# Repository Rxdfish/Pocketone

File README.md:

# Pocketone
A compact midi board that fits into any pocket and still has a lot of features 

Inspiration came from this Repo with brilliant tutorial: [have a look]([https://github.com/SharKingStudios/Starbie/tree/main](https://github.com/KaiPereira/MIDI-Keypad/blob/master/README.md))

# What is this

Pocketone is a project, made for the [Half life](https://halflife.hackclub.com) by Hackclub programm. It is an MIDI keyboard with compact design and lots of features. It can be used to create music inputs for a computer or laptop.

The Board features a Microcontroller, display, buttons, and capacitive sensors in a compact PCB design. It is USB powered and easy to build.

# Project status

The project is half finished but more features and maybe tutorial will come soon.

# Motivation

The main motivation is of course the Half Life (LINK) program by hackclub. It was designed in week three of the project where the task was to create a music PCB. Other than that, I really wanted to design a PCB for a long time now and it definitely won’t be my last one. It was quite som challenge to cook that midi board up and its not nearly finished but im proud of my result.

# Project journaling

Via the [Half life](https://halflife.hackclub.com) by Hackclub programm, several Journal entries have been made either in timelaps form or as written entry to track the project. 

# Assembly

The assembly should be quite beginnerfriendly. The board itself has not many part and is partly prefabricated. All remaining components are easy to be soldered by hand.

# Schematic and components

The board is powered by the Waveshare ESP32-S3-ZERO. It provides the power and data connector with an onboard USB-receptacle. The board also features a keyboard in form of capacitive sensors and a small OLED display. Furthermore it has 3 fader sliders and 8 preassure sensor pads. Everything is made possible by an GPIO expander and a MUX.

# PCB

The PCB is a simple 2 layer PCB. NOthing special about it 

# Firmware

Sadly there is no firmware yet.

# BOM

This is the funding BOM but there is another BOM for all parts and the PCB manufacturing, which is out of budget unfortuenately.

PCB manuf. 
price: 19.30$

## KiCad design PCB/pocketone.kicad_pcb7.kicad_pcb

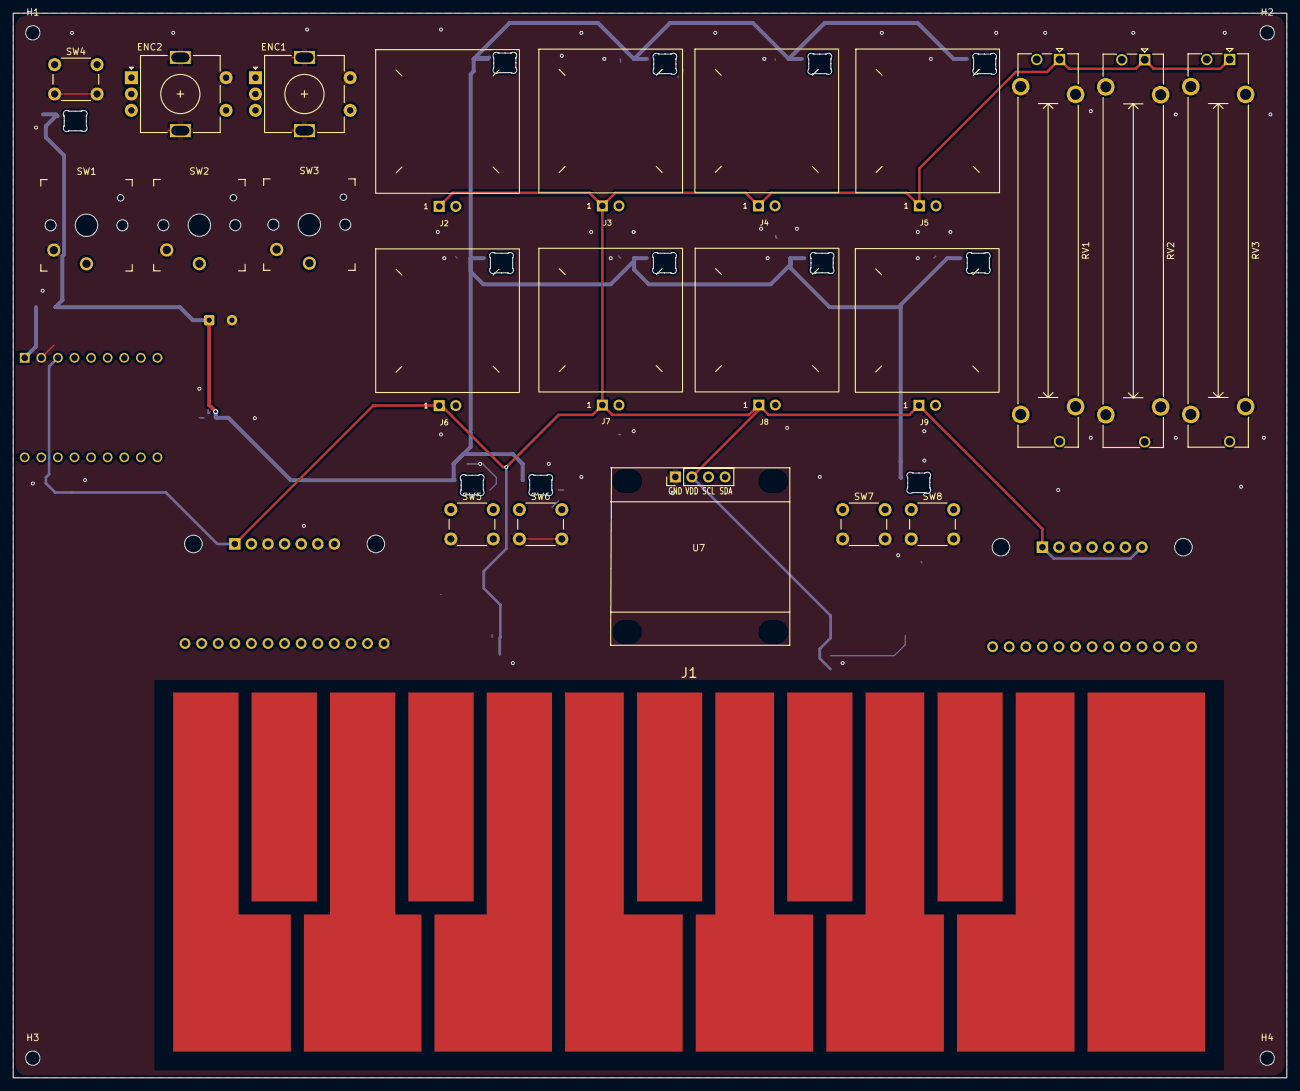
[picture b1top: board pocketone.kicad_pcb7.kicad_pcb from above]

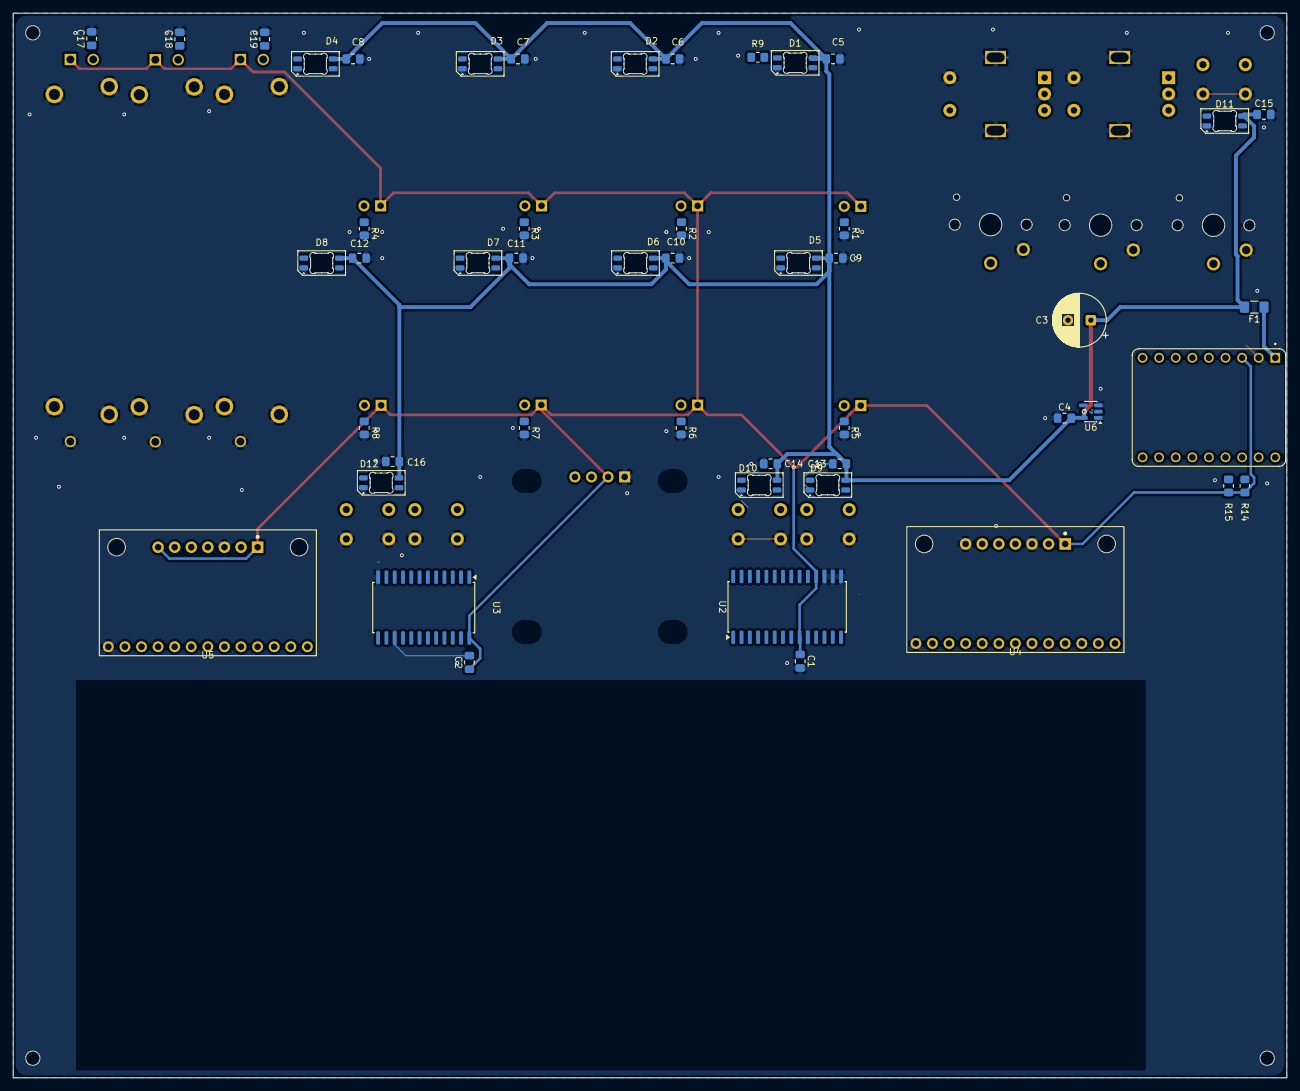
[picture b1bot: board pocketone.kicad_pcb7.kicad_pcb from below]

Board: 2 copper layers, 195.0 x 163.0 mm, 76 parts (49 on the bottom side), 63 nets.

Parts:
C1, C2, C4, C17, C18, C19: 100nF; C_0805_2012Metric_Pad1.18x1.45mm_HandSolder
C3: 470uF; CP_Radial_D8.0mm_P3.50mm
C5, C6, C7, C8, C9, C10, C11, C12, C13, C14, C15, C16: 100n; C_0805_2012Metric_Pad1.18x1.45mm_HandSolder
D1, D2, D3, D4, D5, D6, D7, D8, D9, D10, D11, D12: SK6812MINI-E; LED_SK6812MINI-E_3.2x2.8mm_P1.5mm_ReverseMount
ENC1, ENC2: RotaryEncoder_Switch_MP; RotaryEncoder_Alps_EC11E-Switch_Vertical_H20mm
F1: Polyfuse; Fuse_1206_3216Metric_Pad1.42x1.75mm_HandSolder
H1, H2, H3, H4: MountingHole_2.2mm_M2
J1: CAPACITIVE TOUCH BUTTONS; TouchKeys_1Octave
J2, J3, J4, J5, J6, J7, J8, J9: Conn_01x02; FSR402_Pad_22mm
R1, R2, R3, R4, R5, R6, R7, R8: 10k; R_0805_2012Metric_Pad1.20x1.40mm_HandSolder
R9: 330 O; R_0805_2012Metric_Pad1.20x1.40mm_HandSolder
R14, R15: 4.7kO; R_0805_2012Metric_Pad1.20x1.40mm_HandSolder
RV1, RV2, RV3: Slider; Potentiometer_Bourns_PTA4543_Single_Slide
SW1, SW2, SW3: SW_Push; Kailh Choc Low-Profile Switches
SW4, SW5, SW6, SW7, SW8: SW_Push; SW_PUSH_6mm
U1: Waveshare ESP32-S3-ZERO; Waveshare ESP32-S3-Zero
U2: MCP23017x-x-SO; SOIC-28W_7.5x17.9mm_P1.27mm
U3: CD74HC4067M; SOIC-24W_7.5x15.4mm_P1.27mm
U4, U5: MPR121 BREAKOUT; Adafruit_MPR121_STEMMA_QT
U6: 74AHCT1G125; SOT-23-5
U7: Conn_01x04; Display_128x64_096_I2C

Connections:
+3V3: C1.1, C2.1, J2.1, J3.1, J4.1, J5.1, J6.1, J7.1, J8.1, J9.1, R14.1, R15.2, RV1.1, RV2.1, RV3.1, U1.3V3 (3V3(OUT)), U2.9 (V_{DD}), U2.18 (~RESET), U3.24 (VCC), U4.1 (VIN), U5.1 (VIN), U5.7 (ADDR), U7.2
+5V: F1.1, U1.5V
+5V_LED: C3.1, C4.2, C5.1, C6.1, C7.1, C8.1, C9.1, C10.1, C11.1, C12.1, C13.1, C14.1, C15.1, C16.1, D1.3 (VDD), D2.3 (VDD), D3.3 (VDD), D4.3 (VDD), D5.3 (VDD), D6.3 (VDD), D7.3 (VDD), D8.3 (VDD), D9.3 (VDD), D10.3 (VDD), D11.3 (VDD), D12.3 (VDD), F1.2, U6.5 (VCC)
ENC1_A: ENC1.A, U1.7 (GP7)
ENC1_B: ENC1.B, U1.8 (GP8)
ENC1_SW: ENC1.S1, U2.1 (GPB0)
ENC2_A: ENC2.A, U1.9 (GP9)
ENC2_B: ENC2.B, U1.10 (GP10)
ENC2_SW: ENC2.S1, U2.2 (GPB1)
FADER1: C17.1, RV1.2, U3.23 (I8)
FADER2: C18.1, RV2.2, U3.22 (I9)
FADER3: C19.1, RV3.2, U3.21 (I10)
GND: C1.2, C2.2, C3.2, C4.1, C5.2, C6.2, C7.2, C8.2, C9.2, C10.2, C11.2, C12.2, C13.2, C14.2, C15.2, C16.2, C17.2, C18.2, C19.2, D1.1 (VSS), D2.1 (VSS), D3.1 (VSS), D4.1 (VSS), D5.1 (VSS), D6.1 (VSS), D7.1 (VSS), D8.1 (VSS), D9.1 (VSS), D10.1 (VSS), D11.1 (VSS), D12.1 (VSS), ENC1.C, ENC1.MP, ENC1.S2, ENC2.C, ENC2.MP, ENC2.S2, R1.2, R2.2, R3.2, R4.2, R5.2, R6.2, R7.2, R8.2, RV1.3, RV1.MP (MountPin), RV2.3, RV2.MP (MountPin), RV3.3, RV3.MP (MountPin), SW1.2, SW2.2, SW3.2, SW4.2, SW5.2, SW6.2, SW7.2, SW8.2, U1.GND, U2.10 (V_{SS}), U2.15 (A0), U2.16 (A1), U2.17 (A2), U3.12 (GND), U3.15 (~E), U4.3 (GND), U4.7 (ADDR), U4.20 (GND), U5.3 (GND), U5.20 (GND), U6.1, U6.3 (GND), U7.1
I2C_SCL: R14.2, U1.13 (GP13), U2.12 (SCK), U4.4 (SCL), U5.4 (SCL), U7.3
I2C_SDA: R15.1, U1.12 (GP12), U2.13 (SDA), U4.5 (SDA), U5.5 (SDA), U7.4
KEY_A: J1.10, U4.17 (E2)
KEY_AS: J1.11, U4.18 (E1)
KEY_C: J1.1, U4.8 (E11)
KEY_C2: J1.13, U5.19 (E0)
KEY_CS: J1.2, U4.9 (E10)
KEY_D: J1.3, U4.10 (E9)
KEY_DS: J1.4, U4.11 (E8)
KEY_E: J1.5, U4.12 (E7)
KEY_F: J1.6, U4.13 (E6)
KEY_FS: J1.7, U4.14 (E5)
KEY_G: J1.8, U4.15 (E4)
KEY_GS: J1.9, U4.16 (E3)
KEY_H: J1.12, U4.19 (E0)
LED_DATA: U1.11 (GP11), U6.2
LED_DIN: D1.2 (DIN), R9.2
MUX_S0: U1.2 (GP2), U3.10 (S0)
MUX_S1: U1.3 (GP3), U3.11 (S1)
MUX_S2: U1.4 (GP4), U3.14 (S2)
MUX_S3: U1.5 (GP5), U3.13 (S3)
MUX_SIG: U1.1 (GP1), U3.1 (COM)
unnamed: D1.4 (DOUT), D2.2 (DIN)
unnamed: D2.4 (DOUT), D3.2 (DIN)
unnamed: D3.4 (DOUT), D4.2 (DIN)
unnamed: D4.4 (DOUT), D5.2 (DIN)
unnamed: D5.4 (DOUT), D6.2 (DIN)
unnamed: D6.4 (DOUT), D7.2 (DIN)
unnamed: D7.4 (DOUT), D8.2 (DIN)
unnamed: D8.4 (DOUT), D9.2 (DIN)
unnamed: D9.4 (DOUT), D10.2 (DIN)
unnamed: D10.4 (DOUT), D11.2 (DIN)
unnamed: D11.4 (DOUT), D12.2 (DIN)
unnamed: R9.1, U6.4
unnamed: SW1.1, U2.21 (GPA0)
unnamed: SW2.1, U2.22 (GPA1)
unnamed: SW3.1, U2.23 (GPA2)
unnamed: SW4.1, U2.24 (GPA3)
unnamed: SW5.1, U2.25 (GPA4)
unnamed: SW6.1, U2.26 (GPA5)
unnamed: SW7.1, U2.27 (GPA6)
unnamed: SW8.1, U2.28 (GPA7)
PAD1: J2.2, R1.1, U3.9 (I0)
PAD2: J3.2, R2.1, U3.8 (I1)
PAD3: J4.2, R3.1, U3.7 (I2)
PAD4: J5.2, R4.1, U3.6 (I3)
PAD5: J6.2, R5.1, U3.5 (I4)
PAD6: J7.2, R6.1, U3.4 (I5)
PAD7: J8.2, R7.1, U3.3 (I6)
PAD8: J9.2, R8.1, U3.2 (I7)

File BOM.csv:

Item,Qty,Supplier,Cost/item,Total Cost,link
Estimated total shipping,1,,,$0.00,
"Reference","Qty","Value","DNP","Exclude from BOM","Exclude from Board","Exclude from Simulation","Exclude from Position Files","Footprint","Datasheet"
"C1,C2,C4,C17,C18,C19","6","100nF","","","","","${EXCLUDE_FROM_POS_FILES}","Capacitor_SMD:C_0805_2012Metric_Pad1.18x1.45mm_HandSolder",""
"C3","1","470uF","","","","","${EXCLUDE_FROM_POS_FILES}","Capacitor_THT:CP_Radial_D8.0mm_P3.50mm",""
"C5,C6,C7,C8,C9,C10,C11,C12,C13,C14,C15,C16","12","100n","","","","","${EXCLUDE_FROM_POS_FILES}","Capacitor_SMD:C_0805_2012Metric_Pad1.18x1.45mm_HandSolder",""
"D1,D2,D3,D4,D5,D6,D7,D8,D9,D10,D11,D12","12","SK6812MINI-E","","","","","${EXCLUDE_FROM_POS_FILES}","LED_SMD:LED_SK6812MINI-E_3.2x2.8mm_P1.5mm_ReverseMount","https://www.lcsc.com/datasheet/C5149201.pdf"
"ENC1,ENC2","2","RotaryEncoder_Switch_MP","","","","","${EXCLUDE_FROM_POS_FILES}","Rotary_Encoder:RotaryEncoder_Alps_EC11E-Switch_Vertical_H20mm",""
"F1","1","Polyfuse","","","","","${EXCLUDE_FROM_POS_FILES}","Fuse:Fuse_1206_3216Metric_Pad1.42x1.75mm_HandSolder",""
"J1","1","CAPACITIVE TOUCH BUTTONS","","","","","${EXCLUDE_FROM_POS_FILES}","MIDI_Keypad:TouchKeys_1Octave",""
"J2,J3,J4,J5,J6,J7,J8,J9","8","Conn_01x02","","","","","${EXCLUDE_FROM_POS_FILES}","MIDI_Keypad:FSR402_Pad_22mm",""
"R1,R2,R3,R4,R5,R6,R7,R8","8","10k","","","","","${EXCLUDE_FROM_POS_FILES}","Resistor_SMD:R_0805_2012Metric_Pad1.20x1.40mm_HandSolder",""
"R9","1","330 O","","","","","${EXCLUDE_FROM_POS_FILES}","Resistor_SMD:R_0805_2012Metric_Pad1.20x1.40mm_HandSolder",""
"R14,R15","2","4.7kO","","","","","${EXCLUDE_FROM_POS_FILES}","Resistor_SMD:R_0805_2012Metric_Pad1.20x1.40mm_HandSolder",""
"RV1,RV2,RV3","3","Slider","","","","","${EXCLUDE_FROM_POS_FILES}","Potentiometer_THT:Potentiometer_Bourns_PTA4543_Single_Slide",""
"SW1,SW2,SW3","3","SW_Push","","","","","${EXCLUDE_FROM_POS_FILES}","Hackclub Footprints:Kailh Choc Low-Profile Switches",""
"SW4,SW5,SW6,SW7,SW8","5","SW_Push","","","","","${EXCLUDE_FROM_POS_FILES}","Button_Switch_THT:SW_PUSH_6mm",""
"U1","1","Waveshare ESP32-S3-ZERO","","","","","${EXCLUDE_FROM_POS_FILES}","Hackclub Footprints:Waveshare ESP32-S3-Zero",""
"U2","1","MCP23017x-x-SO","","","","","${EXCLUDE_FROM_POS_FILES}","Package_SO:SOIC-28W_7.5x17.9mm_P1.27mm","https://ww1.microchip.com/downloads/aemDocuments/documents/A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"
"U3","1","CD74HC4067M","","","","","${EXCLUDE_FROM_POS_FILES}","Package_SO:SOIC-24W_7.5x15.4mm_P1.27mm","http://www.ti.com/lit/ds/symlink/cd74hc4067.pdf"
"U4,U5","2","MPR121 BREAKOUT","","","","","${EXCLUDE_FROM_POS_FILES}","MIDI_Keypad:Adafruit_MPR121_STEMMA_QT","https://learn.adafruit.com/adafruit-mpr121-12-key-capacitive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"
"U6","1","74AHCT1G125","","","","","${EXCLUDE_FROM_POS_FILES}","Package_TO_SOT_SMD:SOT-23-5","http://www.ti.com/lit/sg/scyt129e/scyt129e.pdf"
"U7","1","Conn_01x04","","","","","${EXCLUDE_FROM_POS_FILES}","Imported Parts 2:Display_128x64_096_I2C",""
